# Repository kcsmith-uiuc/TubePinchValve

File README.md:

# TubePinchValve
This device uses an Arduino microcontroller to actuate a servo that is used to pinch one tube while another tube is left unpinched, thus acting as a three-way valve that eliminates internal fluid volume and internal seals.  As many as four such "valves" can be controlled at a given time based on a trigger signal received by the Arduino.  A custom printed circuit board (PCB) that interfaces between the Arduino and the associated servos is included with this repository, along with CAD drawings for 3D printable mounts that fix two tubes, a servo motor, and a lever in place for the purpose of fluid switching.  In total, the entire device can be made for approximately 100 USD, as of May 6, 2025.  This device has found particular use in the Smith Lab for directing water flow through battery-based electrochemical desalination and carbon-capture processes, as described and used in the following references:

[1] [Reale, E. R., Regenwetter, L., Agrawal, A., Dardón, B., Dicola, N., Sanagala, S., & Smith, K. C. (2021). Low porosity, high areal-capacity Prussian blue analogue electrodes enhance salt removal and thermodynamic efficiency in symmetric Faradaic deionization with automated fluid control. Water Research X, 13, 100116.](https://doi.org/10.1016/j.wroa.2021.100116)

[2] [Do, V. Q., Reale, E. R., Loud, I. C., Rozzi, P. G., Tan, H., Willis, D. A., & Smith, K. C. (2023). Embedded, micro-interdigitated flow fields in high areal-loading intercalation electrodes towards seawater desalination and beyond. Energy & Environmental Science, 16(7), 3025–3039.](https://doi.org/10.1039/d3ee01302b)

[3] [Rahman, M. H., Loud, I. C., Do, V. Q., Hamid, M. A., & Smith, K. C. (2025). Tapered, Interdigitated Channels for Uniform, Low-Pressure Flow through Porous Electrodes for Desalination and Beyond. Electrochimica Acta, 514, 145632.](https://doi.org/10.1016/j.electacta.2024.145632)

[4] Rozzi, P. G., Lee, J., Do, V. Q., Arthur, T. S., Roberts, C., & Smith, K. C. (2025), Toward Low-Energy Direct-Air CO2 Capture by Reversible Proton-Intercalation Mediated Alkalization, in review.

Using the TubePinchValve device, the [Smith Lab @ UIUC](https://kcsmith.mechse.illinois.edu/) was the [first to demonstrate seawater-level desalination using a battery-based process employing cation-intercalation electrodes](https://news.illinois.edu/mechanical-engineers-lend-fresh-insight-into-battery-based-desalination-technology/) [2,3] and the first to demonstrate capture of 400 ppm CO<sub>2</sub>, as in capturing CO<sub>2</sub> from air, using a battery-based process employing proton-intercalation electrodes [4].  For such processes, a trigger signal sent to the Arduino from a potentiostat that controls electrochemical cycling is used to initiate the switching of two valves that feed liquid flow to two electrodes (i.e., inlet valves), as shown in the video below.  After a pre-specified delay period, two other outlet valves that direct the outflow from the same two electrodes are then switched.  By controlling the delay between the switching of inlet valves and outlet valves, apparent "mixing" between ion-diluted and -concentrated streams is minimized, so as to maximize process ion transfer [1-4].  At present, this repository provides a beta version for the TubePinchValve device, as the present PCB is still under development.

https://github.com/user-attachments/assets/45983bcd-0c9a-48d1-a0b0-8a49e22e287c

**CITE THIS DEVICE AND REPOSITORY AS:**
- Smith, K. C., Egly, C., Do, V. Q., & Rahman, M. H. (2025). TubePinchValve. GitHub. https://github.com/kcsmith-uiuc/TubePinchValve 
- Reale, E. R., Regenwetter, L., Agrawal, A., Dardón, B., Dicola, N., Sanagala, S., & Smith, K. C. (2021). Low porosity, high areal-capacity Prussian blue analogue electrodes enhance salt removal and thermodynamic efficiency in symmetric Faradaic deionization with automated fluid control. Water Research X, 13, 100116. https://doi.org/10.1016/j.wroa.2021.100116

**DESCRIPTION:**
The TubePinchValve device seeks to control the flow of small liquid volumes in a simple, precise, and cost-effective manner by using a servo motor to pinch one of two flexible tubes through which water is flowed.  The single valve is comprised of (1) servo motor, (2) two tubes, (3) a 3D-printable mount, and (4) a microcontroller (e.g., an Arduino). By inserting tubes into either side of the mount, and connecting their inputs to separate pumps, the device acts as a three-way valve. When functioning as a valve, the servo rotates between two positions, pinching off either of the two flows of interest. This functionality allows for rapid, precise switching of flows with little-to-no cross-flow.  This GitHub page provides open-source documentation for the reproduction, modification, and procurement of such three-way valves.

**DESIGN:**
Figure 1 below shows the various electrical and mechanical components that comprise the TubePinchValve assembly: 
- 1 3D printed servo mount
- 1 DS3225 25KG Large Torque Digital Servo with Lever
- 2 small diameter tubes of your choice, such as those used with peristaltic pumps
- 1 Arduino MEGA
- 1 custom PCB
    - 1 Relay
    - 1 Barrel Jack

<p align="center">

Figure 2 below shows the experimental stand that is used to integrate TubePinchValves with an electrochemical flow cell.  The Stand.f3d file in this repository is a Fusion 360 CAD model of the stand.  The StandParts.ai file in this repository is an Adobe Illustrator file that can be used to laser cut the various pieces that comprise the stand:
- 1: Main Base Platform
- 2 and 3: Support Column
- 4: Servo Mount Clamp
- 5: Platform for Flow Cell

<p align="center">

**BILL OF MATERIALS:**
- Servo motor with lever (Example: [DS3225 25KG Large Torque Digital Servo](https://www.amazon.com/RCmall-Digital-Waterproof-Robotic-Crawler/dp/B09PZSR2Q3/ref=sr_1_6?keywords=25kg%2Bservo%2B4%2Bpack&qid=1678895816&sprefix=25kg%2Bservo%2B4%2Caps%2C107&sr=8-6&ufe=app_do%3Aamzn1.fos.006c50ae-5d4c-4777-9bc0-4513d670b6bc&th=1))
- PCB: Use your favorite custom PCB ordering website, such as JLCPCB.com.
  - 1 Relay (Example: [2449-J1021AS35VDC.20-ND RELAY GEN PURPOSE SPST 3A 5V](https://www.digikey.com/en/products/detail/cit-relay-and-switch/J1021AS35VDC-20/14002155))
  - 1 Barrel Jack (Example: [2.1 mm DC barrel jack](https://www.adafruit.com/product/373?gQT=1))
- Tubing (Example: [Masterflex® L/S® Precision Pump Tubing, Versilon™ A-60-G, L/S 13](https://www.avantorsciences.com/us/en/product/NA5143380/masterflex-l-s-precision-pump-tubing-versilontm-a-60-n-avantor))
- 3D printing feedstock of your choice for servo mounts
- Acrylic or plywood sheeting for experimental stand
- ServoMount.f3d and ServoMount.stl CAD files for 3D-printable servo mounts
- Stand.f3d CAD file and StandParts.ai Adobe Illustrator file for experimental stand

**BUILD INSTRUCTIONS:**
1. Order all parts in the DESIGN section.
2. If modifications are not necessary, take the *.zip file in this GitHub repository named: Recirculation_Aparatus_PCB_V4-B_Cu.zip, and drop it into your favorite PCB manufacturing website.  If modifications to the PCB are necessary, load the relevant PCB files including *.drl files into your preferred PCB CAD software (e.g., KiCad), and export them as manufacturing files. Combine these files into a single *.zip file, and drap and drop them into your favorite PCB manufacturing website. 
3. Upon receipt of components, solder the barrel jack and relay onto the PCB, and connect each servo to the Arduino.
4. Connect each servo, lever, and pair of tubes to the mount of interest.  If desired, connect the mounts to the experimental stand.
5. Calibrate servo positions by running the Servo_pinching_calibration/Servo_pinching_calibration.ino Arduino script to produce optimal tube pinching.  In this script the user can adjust servo angles for two distinct states of each TubePinchValve.  The script makes use of [Arduino's servo.h library](https://docs.arduino.cc/libraries/servo/).
6. After calibrating the preceding script, the user can then use the same file to initiate periodic switching subject to a trigger signal of interest.

**ACKNOWLEDGMENTS:**
Support for Vu Q. Do, Md Habibur Rahman, and Kyle C. Smith is acknowledged from the US Office of Naval Research (Award no. N00014-22-1-2577).  Support for Chris Egly via a Research Experience for Undergraduates (REU) is acknowledged from the US National Science Foundation (Award no. 1931659).

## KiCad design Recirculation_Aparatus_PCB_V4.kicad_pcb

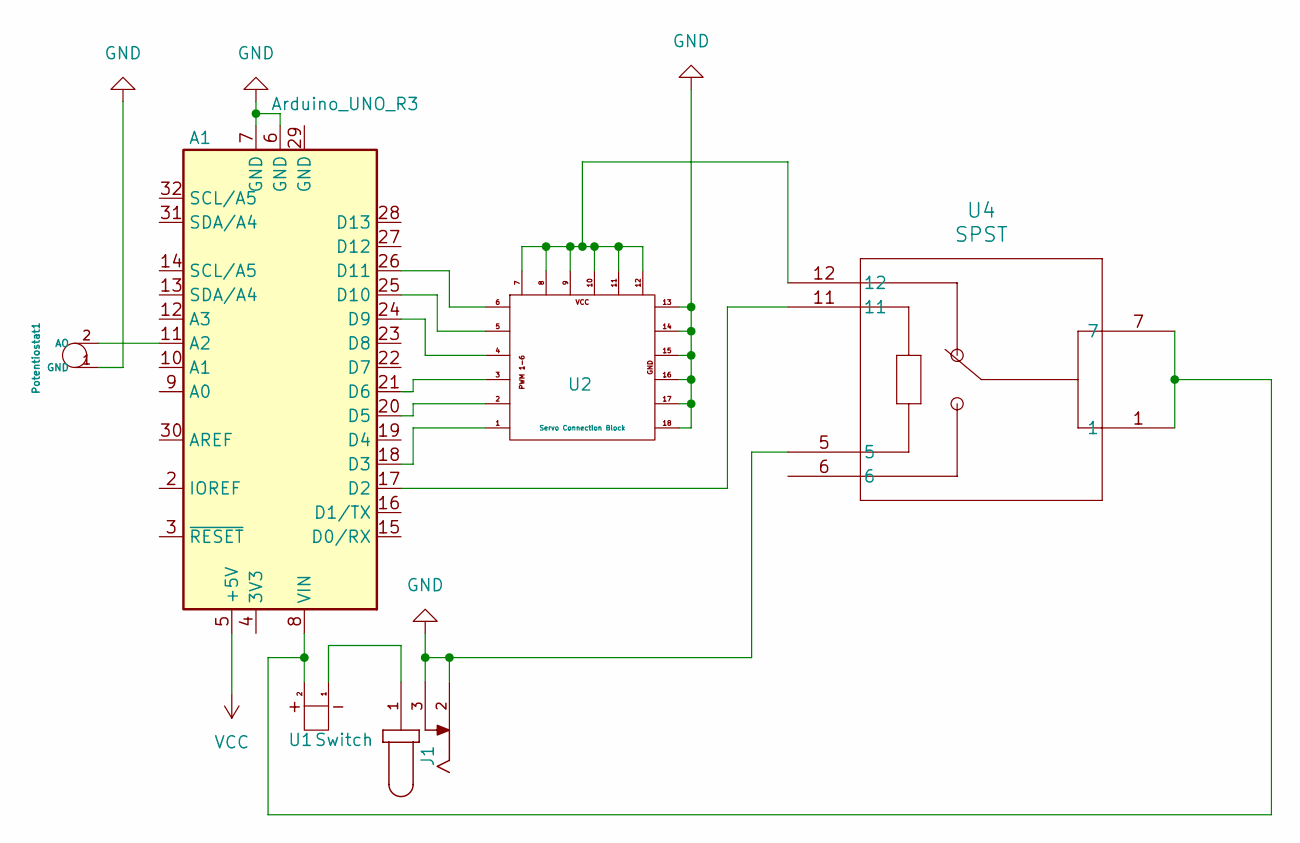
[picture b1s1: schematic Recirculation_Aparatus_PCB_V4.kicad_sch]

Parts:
A1: Arduino_UNO_R3
J1: PJ-202B; CUI_PJ-202B; PART_REV 1.02
Potentiostat1: Potentiometer
U1: Switch
U2: Servo Connection Block
U4: SPST; RELAY6_J1021CS312VDC.20_CRS

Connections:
GND: A1.6 (GND), A1.7 (GND), J1.2, J1.3, Potentiostat1.1 (GND), U2.13, U2.14, U2.15, U2.16, U2.17, U2.18, U4.5
unnamed: A1.11 (A2), Potentiostat1.2 (AO)
unnamed: A1.17 (D2), U4.11
unnamed: A1.18 (D3), U2.1
unnamed: A1.20 (D5), U2.2
unnamed: A1.21 (D6), U2.3
unnamed: A1.24 (D9), U2.4
unnamed: A1.25 (D10), U2.5
unnamed: A1.26 (D11), U2.6
unnamed: A1.8 (VIN), U1.2, U4.1, U4.7
unnamed: J1.1, U1.1
unnamed: U2.7, U2.8, U2.9, U2.10, U2.11, U2.12, U4.12
VCC: A1.5 (+5V)

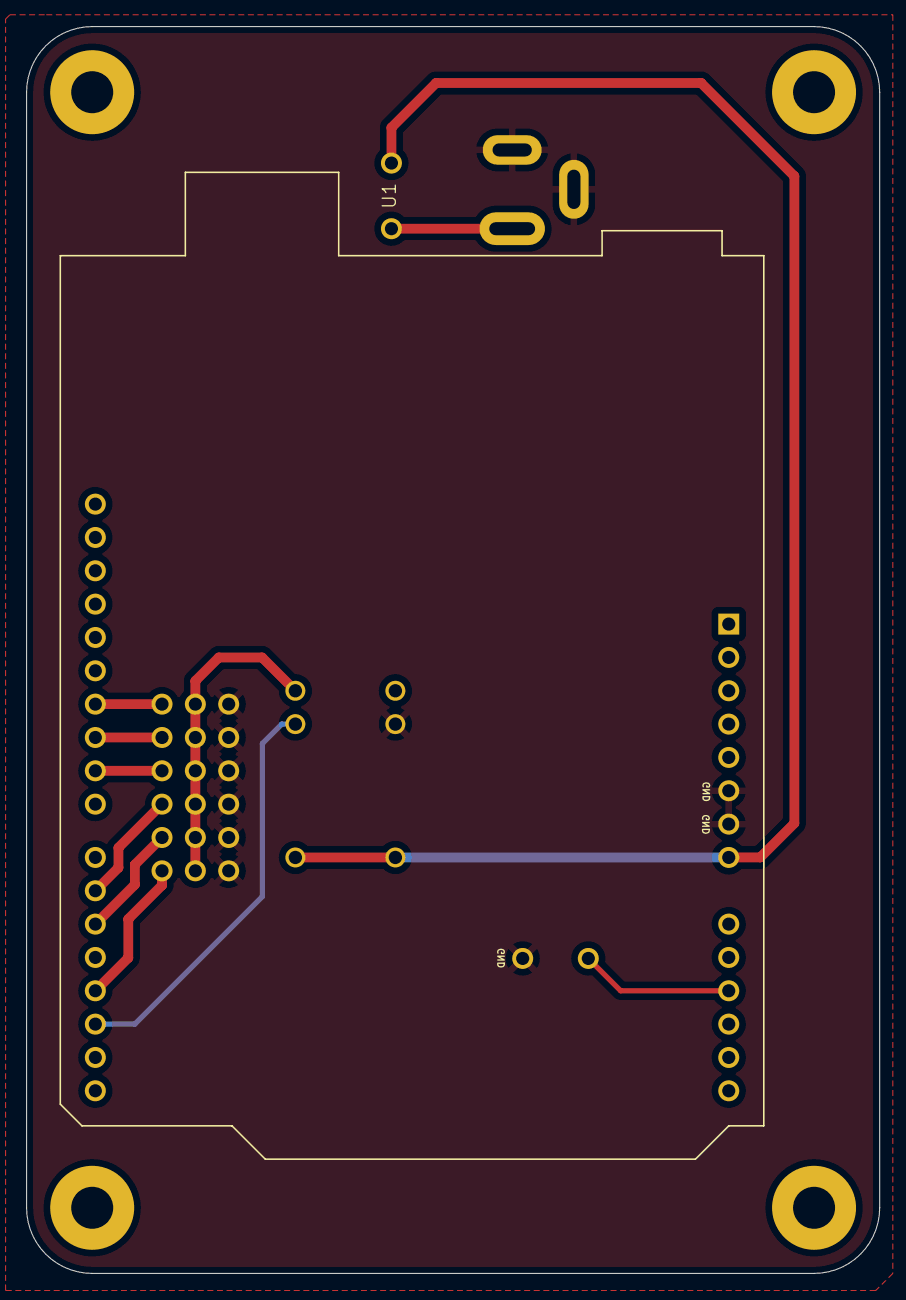
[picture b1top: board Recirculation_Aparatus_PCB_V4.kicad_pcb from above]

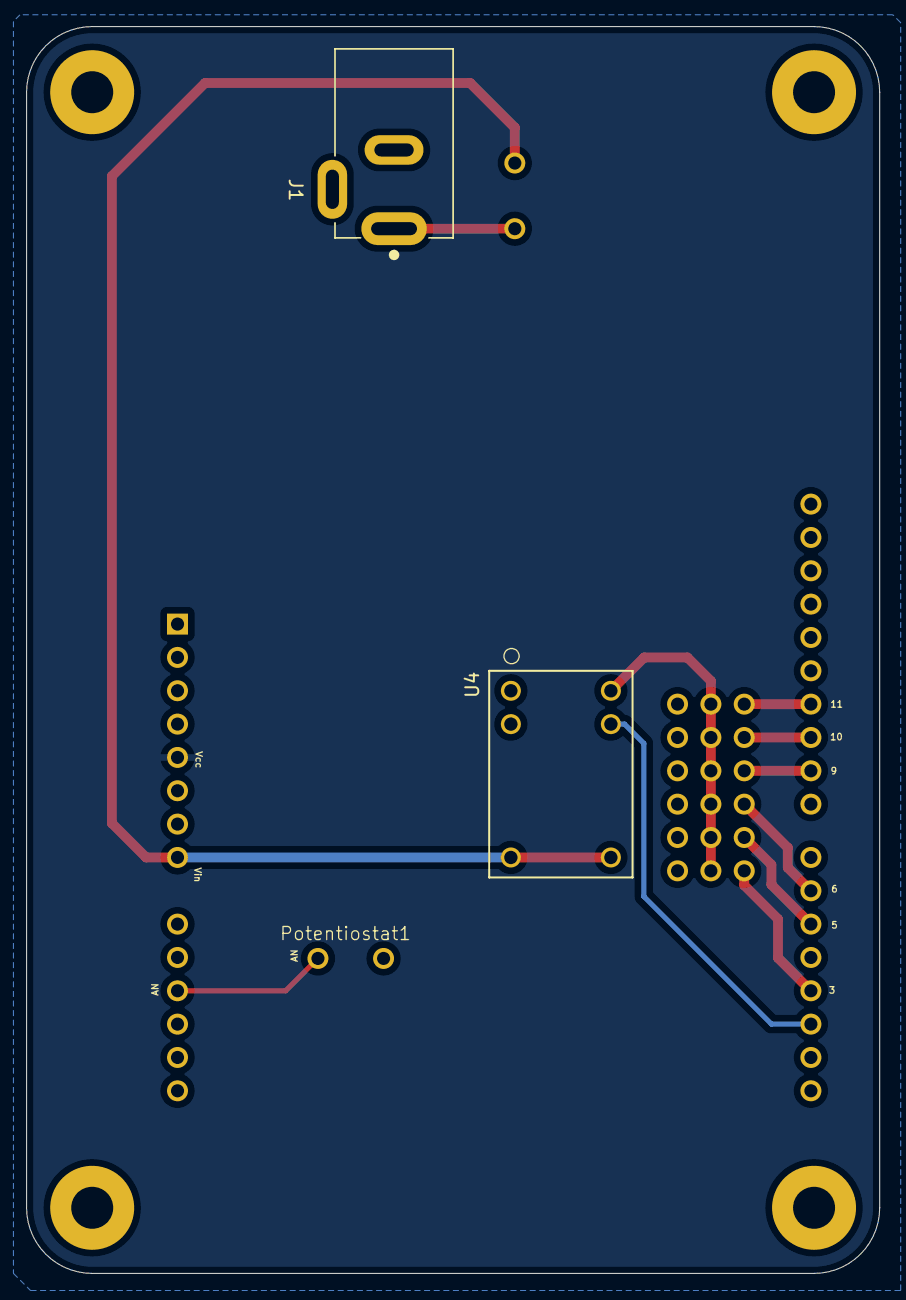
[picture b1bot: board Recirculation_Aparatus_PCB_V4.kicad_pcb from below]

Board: 2 copper layers, 65.0 x 95.0 mm, 6 parts (2 on the bottom side), 12 nets.

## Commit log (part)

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2025-04-13 Update README.md
    readme created
2025-04-13 Add files via upload
    PCB files for editing
2025-04-13 Add files via upload
    PCB manufacturing files
2025-04-13 Update README.md
    Update
